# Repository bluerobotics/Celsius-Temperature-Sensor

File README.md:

# Celsius Temperature Sensor

Arduino software library is available [here](http://github.com/bluerobotics/BlueRobotics_TSYS01_Library/).

The schematic and board layout are designed in EagleCAD.

## Description

High accuracy, fast time response subsea temperature sensor with I<sup>2</sup>C interface. It has a measurement accuracy of just &plusmn;0.1&deg;C.

The sensor is the Measurement Specialties TSYS01, It comes standard with a 4-pin DF13 connector and compatible with most DroneCode compatible boards including the APM2.6, PixHawk, and others.

## Features

* &plusmn;0.1&deg;C Accuracy
* Standard DF13 connector for connection to DroneCode boards such as APM, PixHawk, Navio2, etc.
* Sealed in a bulkhead penetrator for easy installation into any 10mm hole

## Compatibility

The Celsius sensor is compatible with any device with 3.3V I<sup>2</sup>C logic. When using with a 5V device, such as an Arduino Uno, it is necessary to use a logic level converter.

## Configuration

The sensor is mounted on a PCB that extends into the water and is sealed from water with a thick layer of thermally conductive epoxy. This mounting method minimizes heat capacitance and ensures a fast time-response.

## Ratings

For further information please see the [TSYS01 Data Sheet](http://meas-spec.com/downloads/TSYS01_Digital_Temperature_Sensor.pdf).

**Electrical:**

| **Item**       | **Condition**   | **Value**           |
| ---: | :---: | --- |
| Supply Voltage | -              | 3.3 to 5.5 volts    |
| I<sup>2</sup>C Logic Voltage (SDA and SCL) | - | 3.3 volts |
| Peak Current   | - | 1.4 mA   |

**Temperature:**

| **Item** | **Condition** | **Value** |
| ---: | :---: | --- |
| Operating Temperature | - | -40 to +125&deg;C |
|Storage Temperature | - | -55 to +150&deg;C |
|Absolute Accuracy   | From -5 to 50&deg;C | +/- 0.1&deg;C      |
|                    | From -40 to 125&deg;C |  +/- 0.5&deg;C   |

**Physical:**

| **Item** | **Condition** |
| ---: | :--- | 
| Wire Colors    | Green - I<sup>2</sup>C Clock (SCL, 3.3V) |
|                | White - I<sup>2</sup>C Data (SDA, 3.3V)  |
|                | Red - Positive (3.3-5.5V) |
|                | Black - Ground          |
| Overall Length | 56.1 mm |
| Thread Size    | M10x1.5 20 mm threaded |
| Recommended Through Hole Size | 10-11 mm |
| Wrench Flats   | 16 mm |

## Physical Specifications

* Bulkhead hole size: 10-10.5mm
* Wire length: 11" (280mm)

## License

The Celsius Pressure Sensor Hardware Design is released under the MIT License.

## Revision History

0.0 - Under development

0.1 - First production version (marked with rev3)

0.2 - Minor layout changes (marked with rev4)

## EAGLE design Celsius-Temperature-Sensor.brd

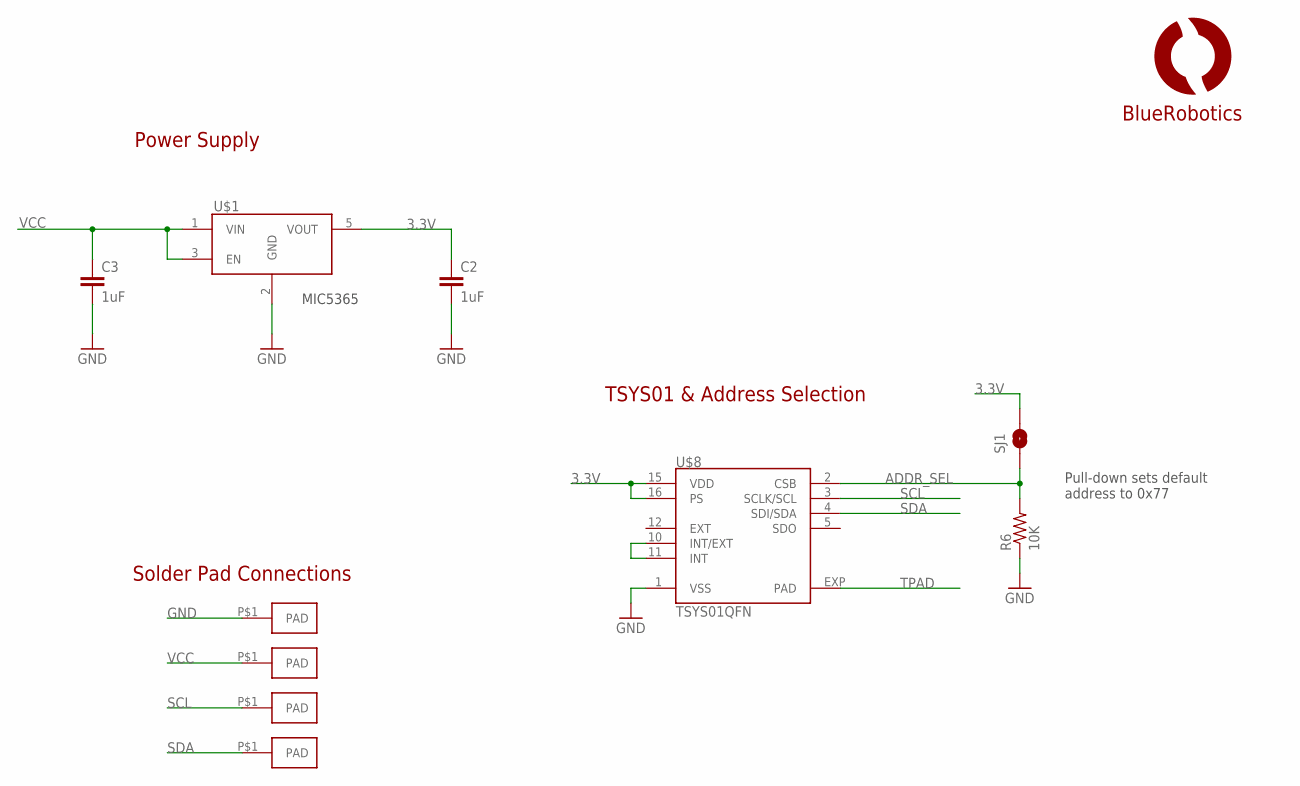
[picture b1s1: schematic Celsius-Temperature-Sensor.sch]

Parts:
C2, C3: 1uF; C0402
R6: 10K; R0402
SJ1: JUMPER-PAD-2-NO; PAD-JUMPER-2-NO_NO_SILK
U$1: VREG-MIC5365; SC70-5L
U$3, U$4, U$5, U$6: PAD1.5X3MM; PAD-1.5X3MM
U$7: LOGOBR-LOGO-S; BR-LOGO-SMALL
U$8: TSYS01QFN; QFN16-4X4

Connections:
3.3V: C2.1, SJ1.2, U$1.5 (VOUT), U$8.15 (VDD), U$8.16 (PS)
ADDR_SEL: R6.2, SJ1.1, U$8.2 (CSB)
GND: C2.2, C3.2, R6.1, U$1.2 (GND), U$3.P$1, U$8.1 (VSS)
unnamed: U$8.10 (INT/EXT), U$8.11 (INT)
SCL: U$5.P$1, U$8.3 (SCLK/SCL)
SDA: U$6.P$1, U$8.4 (SDI/SDA)
TPAD: U$8.EXP (PAD)
VCC: C3.1, U$1.1 (VIN), U$1.3 (EN), U$4.P$1

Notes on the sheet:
Solder Pad Connections
TSYS01 & Address Selection
Power Supply
MIC5365
Pull-down sets default address to 0x77

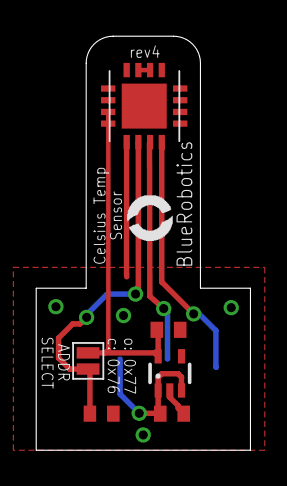
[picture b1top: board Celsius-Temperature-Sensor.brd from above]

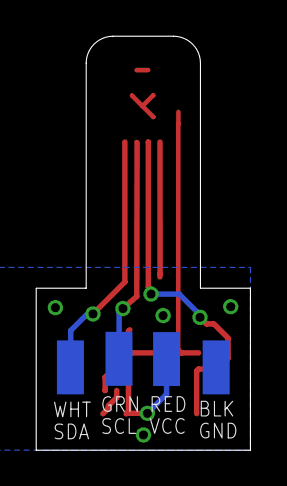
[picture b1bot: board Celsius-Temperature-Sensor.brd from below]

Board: 2 copper layers, 11.9 x 23.0 mm, 11 parts (4 on the bottom side), 7 nets.

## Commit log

2015-11-01 Added base initial files. The board outline is about to change dramatically.
2015-11-01 Updated to new board outline. Still needs some fillets in the corners for machining.
2015-11-02 Updated frame.
2015-11-04 Updated zener to LDO.
2015-11-16 Fixed incorrect regulator footprint. Stupid mistake.
2015-12-16 Removed diode because it caused a large enough Vf to drop voltage outside of range needed to achieve high accuracy Acc1. Also added a few ground vias. Ordering production version from this revision.
2016-01-10 Added PDF schematic, updated readme.
2016-01-18 Fixed for compatibility with DroneCode autopilots.
    Removed logic level converters.
2016-01-18 Updated PDF.
2016-01-24 README: Copied Bar30 and adjusted for Celsius
2016-01-24 README: Typo
2016-01-24 README: Link update
2016-01-26 Update tables
2016-01-26 Fixed table markdown.
2016-01-26 Fixed README formatting.
2019-05-31 update format markdown

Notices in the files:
parts and their libraries:
SparkFun-Passives: Licensing: Creative Commons ShareAlike 4.0 International - https://creativecommons.org/licenses/by-sa/4.0
